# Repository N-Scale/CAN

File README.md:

Ich baue und entwickle Hard- und Software für das Märklin CAN System, weitere Informationen auf  <a href="https://www.stummiforum.de/"> stummiforum.de </a>

Viele Layouts sind Weiterentwicklungen oder Anpassungen an bestehenden Dateien aus dem MaeCAN Projekt.
Hier möchte ich gerne mein Daten mit euch Teilen damit alle die das Märklin CAN System einsetzen wollen davon profitieren können.

Ich versuche die Komponenten an eigener Hardware zu testen, jedoch habe ich nur begrenzt 
Zugriff auf verschiedene Steuereinheiten. Ich kann also nur mit meiner Hardware die Funktionen der Komponenten testen.
Der Nachbau und die Benutzung der Hardware geschieht auf eigene Gefahr, ich hafte nicht für Schäden, die der Anwender oder
Dritte durch die Verwendung verursachen.

Alle Daten sind Sie sind lizensiert unter der <a href="https://creativecommons.org/licenses/by-sa/4.0/de">"Creative Commons Attribution Share-Alike" Lizenz</a> - die eine persönliche und kommerzielle Weiterverwertung erlaubt, solange in angemessener Weise die Urheberschaft erwähnt wird und die abgeleitete Arbeit unter der gleichen Lizenz steht.

<br />This work is licensed under a <a rel="license" href="http://creativecommons.org/licenses/by-sa/4.0/">Creative Commons Attribution-ShareAlike 4.0 International License</a>.

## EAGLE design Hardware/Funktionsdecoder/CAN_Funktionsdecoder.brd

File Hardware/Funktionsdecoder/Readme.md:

Funktionsdecoderaufsatz für das Basisboard.

Ich versuche die Komponenten an eigener Hardware zu testen, jedoch habe ich nur begrenzt 
Zugriff auf verschiedene Steuereinheiten. Ich kann also nur mit meiner Hardware die Funktionen der Komponenten testen.
Der Nachbau und die Benutzung der Hardware geschieht auf eigene Gefahr, ich hafte nicht für Schäden, die der Anwender oder
Dritte durch die Verwendung verursachen.

Alle Daten sind Sie sind lizensiert unter der <a href="https://creativecommons.org/licenses/by-sa/4.0/de">"Creative Commons Attribution Share-Alike" Lizenz</a> - die eine persönliche und kommerzielle Weiterverwertung erlaubt, solange in angemessener Weise die Urheberschaft erwähnt wird und die abgeleitete Arbeit unter der gleichen Lizenz steht.

<br />This work is licensed under a <a rel="license" href="http://creativecommons.org/licenses/by-sa/4.0/">Creative Commons Attribution-ShareAlike 4.0 International License</a>.

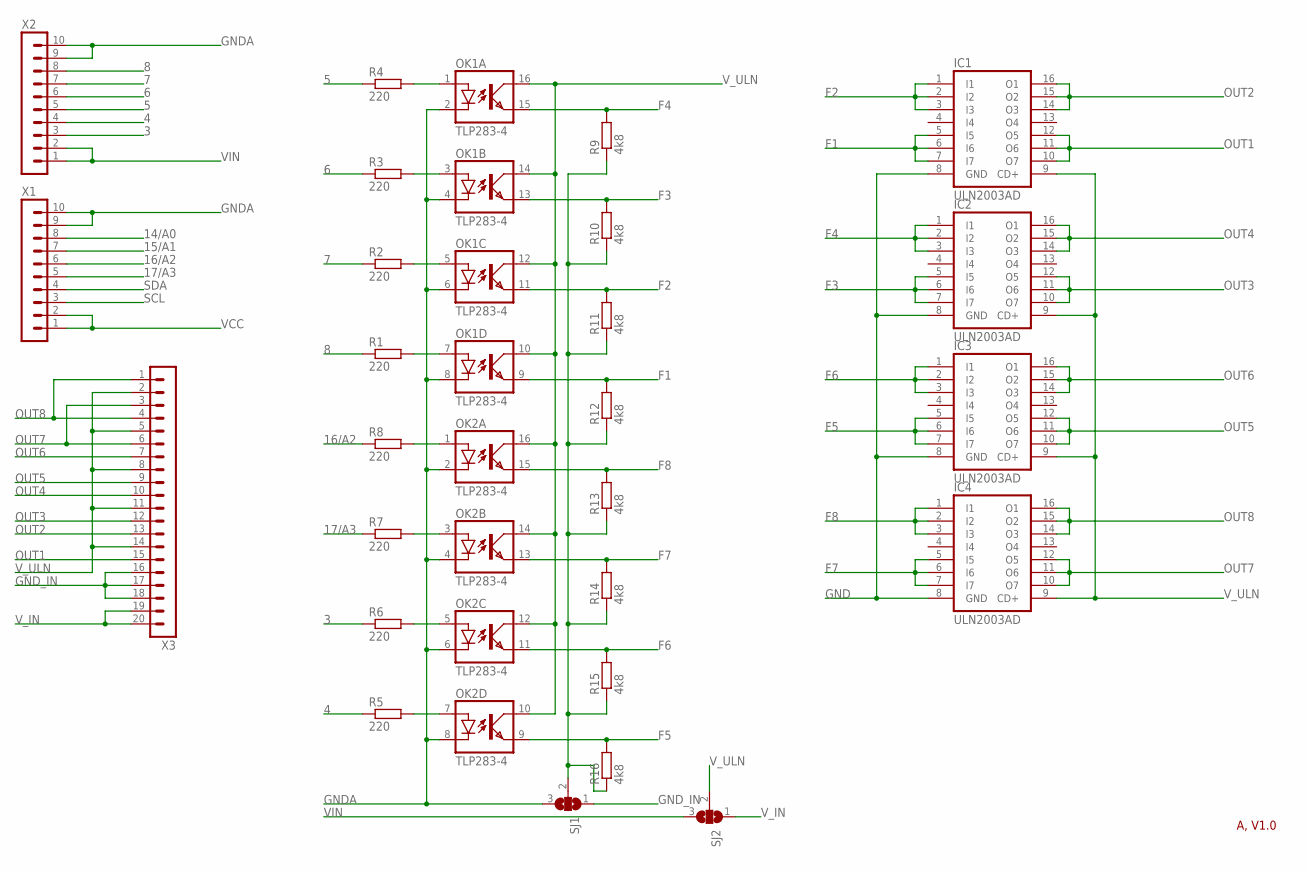
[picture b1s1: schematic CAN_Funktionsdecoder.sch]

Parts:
IC1, IC2, IC3, IC4: ULN2003AD; SO16
OK1, OK2: TLP283-4; MINI-FLAT-16
R1, R2, R3, R4, R5, R6, R7, R8: 220; R0805
R9, R10, R11, R12, R13, R14, R15, R16: 4k8; R0805
SJ1, SJ2: SJ2W; SJ_2
X1, X2: MA10-1
X3: MA20-1

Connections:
3: R6.1, X2.3
4: R5.1, X2.4
5: R4.1, X2.5
6: R3.1, X2.6
7: R2.1, X2.7
8: R1.1, X2.8
14/A0: X1.8
15/A1: X1.7
16/A2: R8.1, X1.6
17/A3: R7.1, X1.5
F1: IC1.5 (I5), IC1.6 (I6), IC1.7 (I7), OK1.9 (EMIT), R12.2
F2: IC1.1 (I1), IC1.2 (I2), IC1.3 (I3), OK1.11 (EMIT), R11.2
F3: IC2.5 (I5), IC2.6 (I6), IC2.7 (I7), OK1.13 (EMIT), R10.2
F4: IC2.1 (I1), IC2.2 (I2), IC2.3 (I3), OK1.15 (EMIT), R9.2
F5: IC3.5 (I5), IC3.6 (I6), IC3.7 (I7), OK2.9 (EMIT), R16.2
F6: IC3.1 (I1), IC3.2 (I2), IC3.3 (I3), OK2.11 (EMIT), R15.2
F7: IC4.5 (I5), IC4.6 (I6), IC4.7 (I7), OK2.13 (EMIT), R14.2
F8: IC4.1 (I1), IC4.2 (I2), IC4.3 (I3), OK2.15 (EMIT), R13.2
GND: IC1.8 (GND), IC2.8 (GND), IC3.8 (GND), IC4.8 (GND), R9.1, R10.1, R11.1, R12.1, R13.1, R14.1, R15.1, R16.1, SJ1.2
GNDA: OK1.2 (C), OK1.4 (C), OK1.6 (C), OK1.8 (C), OK2.2 (C), OK2.4 (C), OK2.6 (C), OK2.8 (C), SJ1.3, X1.9, X1.10, X2.9, X2.10
GND_IN: SJ1.1, X3.16, X3.17, X3.18
unnamed: OK1.3 (A), R3.2
unnamed: OK1.1 (A), R4.2
unnamed: OK1.5 (A), R2.2
unnamed: OK1.7 (A), R1.2
unnamed: OK2.1 (A), R8.2
unnamed: OK2.3 (A), R7.2
unnamed: OK2.5 (A), R6.2
unnamed: OK2.7 (A), R5.2
OUT1: IC1.10 (O7), IC1.11 (O6), IC1.12 (O5), X3.15
OUT2: IC1.14 (O3), IC1.15 (O2), IC1.16 (O1), X3.13
OUT3: IC2.10 (O7), IC2.11 (O6), IC2.12 (O5), X3.12
OUT4: IC2.14 (O3), IC2.15 (O2), IC2.16 (O1), X3.10
OUT5: IC3.10 (O7), IC3.11 (O6), IC3.12 (O5), X3.9
OUT6: IC3.14 (O3), IC3.15 (O2), IC3.16 (O1), X3.7
OUT7: IC4.10 (O7), IC4.11 (O6), IC4.12 (O5), X3.3, X3.6
OUT8: IC4.14 (O3), IC4.15 (O2), IC4.16 (O1), X3.1, X3.4
SCL: X1.3
SDA: X1.4
VCC: X1.1, X1.2
VIN: SJ2.3, X2.1, X2.2
V_IN: SJ2.1, X3.19, X3.20
V_ULN: IC1.9 (CD+), IC2.9 (CD+), IC3.9 (CD+), IC4.9 (CD+), OK1.10 (COL), OK1.12 (COL), OK1.14 (COL), OK1.16 (COL), OK2.10 (COL), OK2.12 (COL), OK2.14 (COL), OK2.16 (COL), SJ2.2, X3.2, X3.5, X3.8, X3.11, X3.14

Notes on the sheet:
A, V1.0

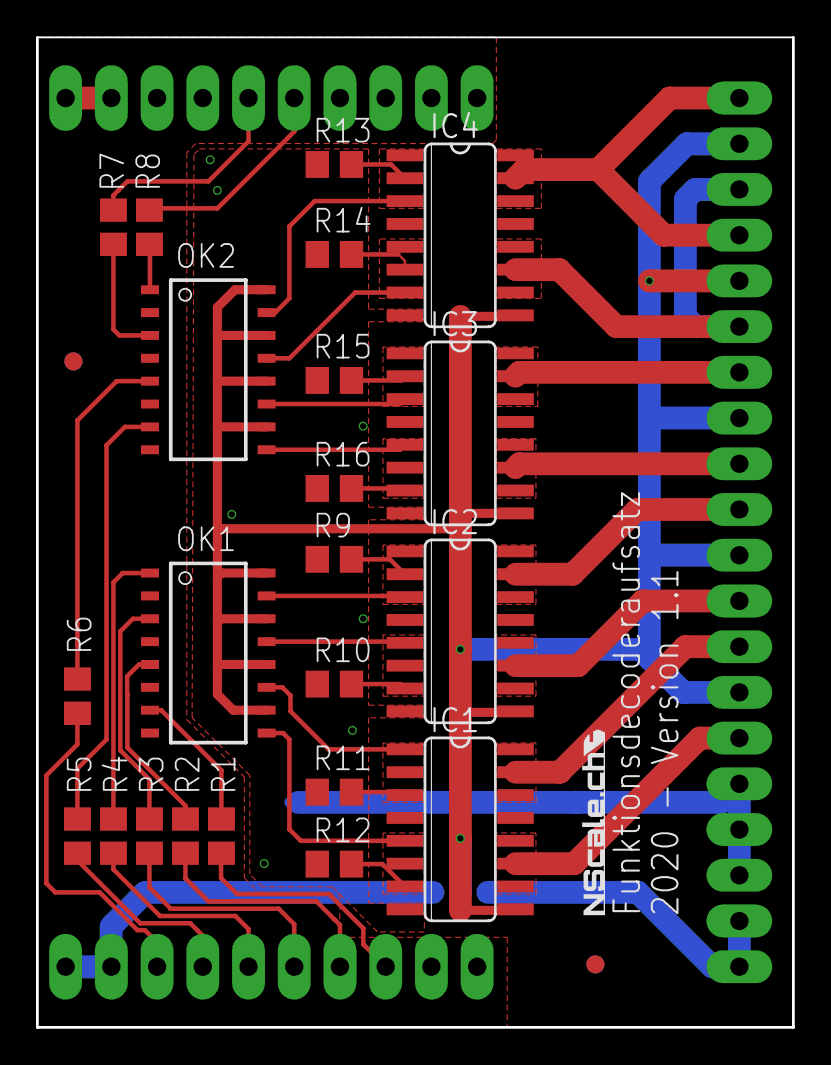
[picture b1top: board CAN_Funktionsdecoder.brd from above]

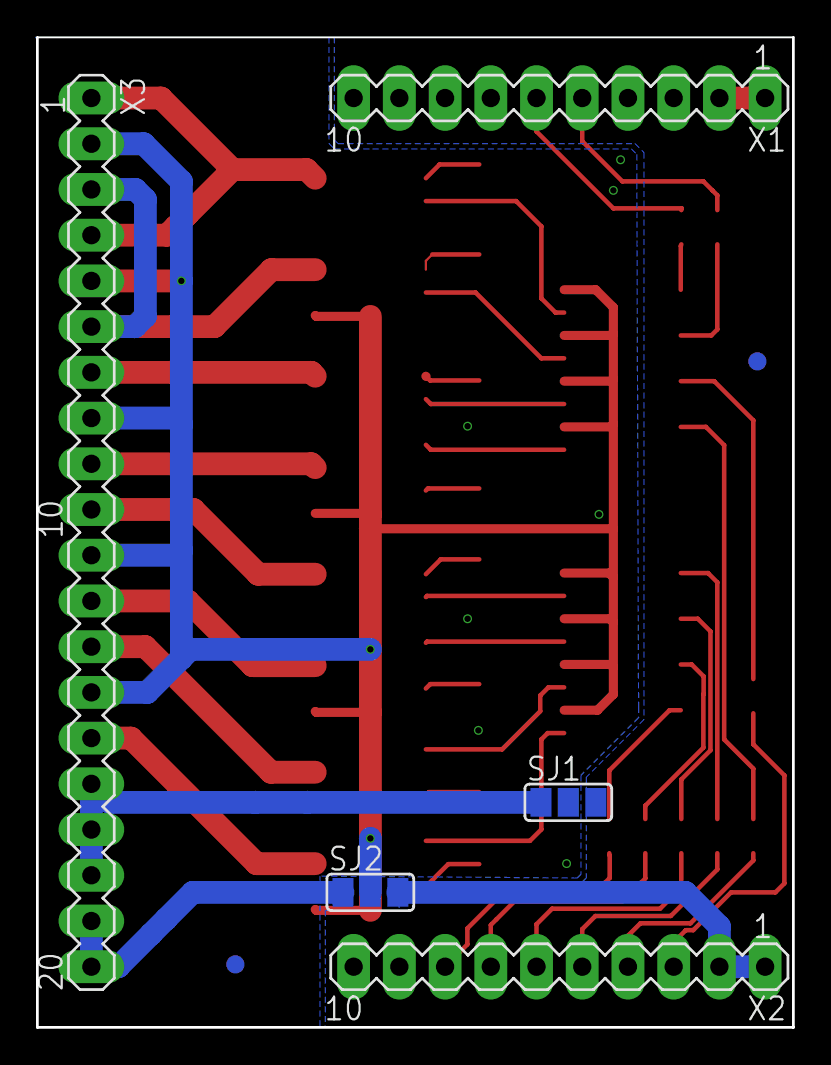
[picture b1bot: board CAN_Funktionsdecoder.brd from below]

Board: 2 copper layers, 42.0 x 55.0 mm, 29 parts (5 on the bottom side), 39 nets.

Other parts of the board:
U$1, U$2: CIRCLE-1MM-3R

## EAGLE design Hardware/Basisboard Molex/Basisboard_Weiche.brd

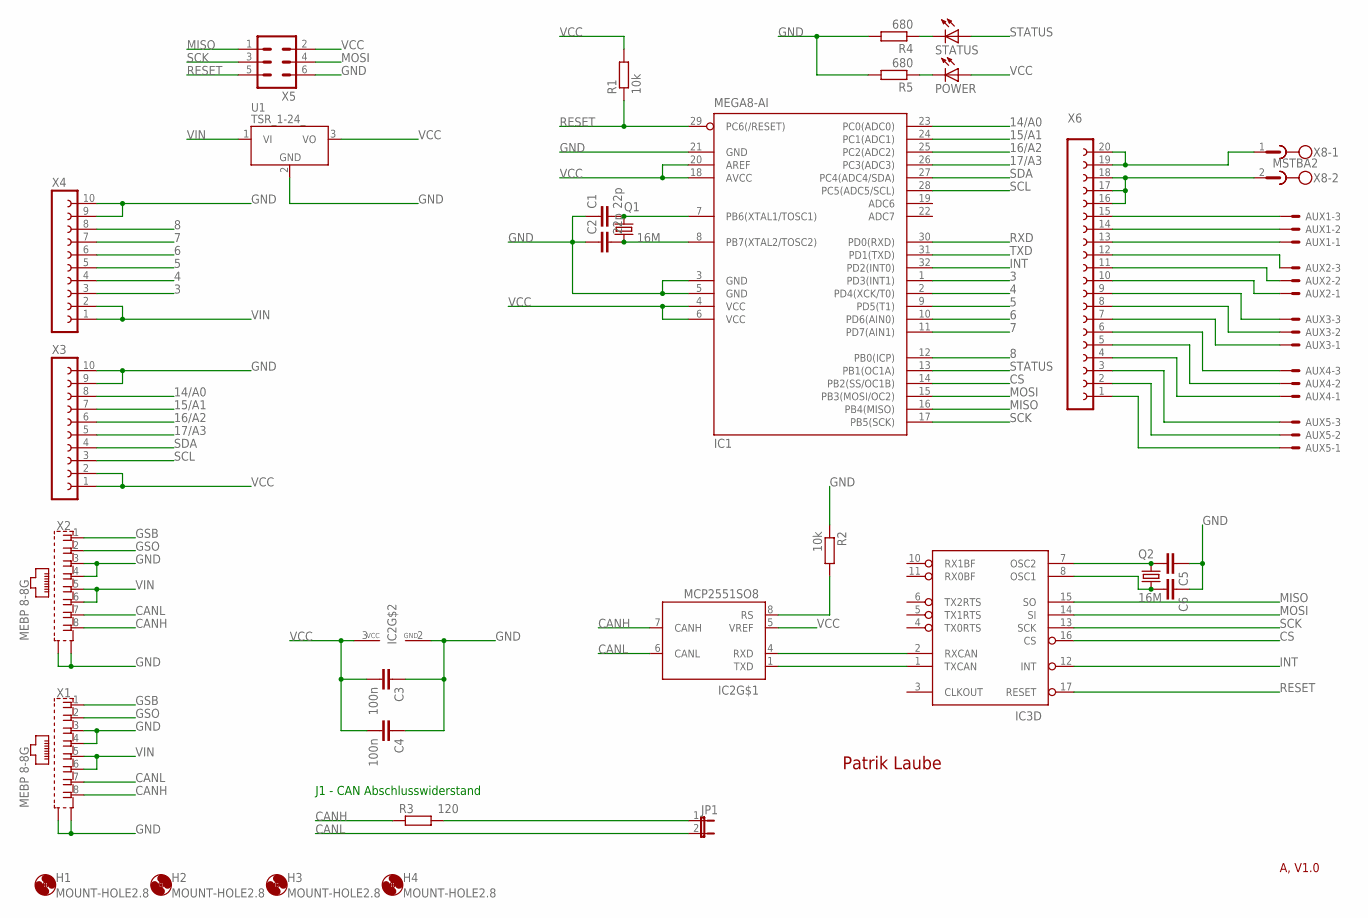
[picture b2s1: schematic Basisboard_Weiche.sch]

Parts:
AUX1, AUX2, AUX3, AUX4, AUX5: 22-27-2031-03; 6410-03
C1, C2: 22p; C1206
C3, C4: 100n; C1206; LCSC_PART C24497
C5, C6: C-EUC1206; C1206
H1, H2, H3, H4: MOUNT-HOLE2.8; 2,8
IC1: MEGA8-AI; TQFP32-08; LCSC_PART C132230
IC2: MCP2551SO8; SO08; LCSC_PART C49558
IC3: MCP2515SO; SO-18W; LCSC_PART C153782
JP1: JP1E; JP1
POWER: LEDCHIPLED_1206; CHIPLED_1206; LCSC_PART C88326
Q1, Q2: 16M; HC49/S
R1, R2: 10k; R1206; LCSC_PART C17902
R3: 120; R1206
R4, R5: 680; R1206
STATUS: LEDCHIPLED_1206; CHIPLED_1206
U1: TSR_1-24_; TSR-1
X1, X2: MEBP 8-8G; XRJF-01A-0-D2A-010
X3, X4: FE10-1; FE10
X5: ML6
X6: FE20-1; FE20
X8: MSTBA2

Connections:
3: IC1.1 (PD3(INT1)), X4.3
4: IC1.2 (PD4(XCK/T0)), X4.4
5: IC1.9 (PD5(T1)), X4.5
6: IC1.10 (PD6(AIN0)), X4.6
7: IC1.11 (PD7(AIN1)), X4.7
8: IC1.12 (PB0(ICP)), X4.8
14/A0: IC1.23 (PC0(ADC0)), X3.8
15/A1: IC1.24 (PC1(ADC1)), X3.7
16/A2: IC1.25 (PC2(ADC2)), X3.6
17/A3: IC1.26 (PC3(ADC3)), X3.5
CANH: IC2.7 (CANH), R3.1, X1.8, X2.8
CANL: IC2.6 (CANL), JP1.2, X1.7, X2.7
CS: IC1.14 (PB2(SS/OC1B)), IC3.16 (CS)
GND: C1.1, C2.1, C3.1, C4.1, C5.1, C6.1, IC1.3 (GND), IC1.5 (GND), IC1.21 (GND), IC2.2 (GND), IC3.9 (GND), R2.1, R4.2, R5.2, U1.2 (GND), X1.3, X1.4, X1.S1 (S), X1.S2 (S), X2.3, X2.4, X2.S1 (S), X2.S2 (S), X3.9, X3.10, X4.9, X4.10, X5.6
GSB: X1.1, X2.1
GSO: X1.2, X2.2
INT: IC1.32 (PD2(INT0)), IC3.12 (INT)
MISO: IC1.16 (PB4(MISO)), IC3.15 (SO), X5.1
MOSI: IC1.15 (PB3(MOSI/OC2)), IC3.14 (SI), X5.4
unnamed: IC2.8 (RS), R2.2
unnamed: JP1.1, R3.2
unnamed: IC2.4 (RXD), IC3.2 (RXCAN)
unnamed: AUX1.1, X6.13
unnamed: AUX1.2, X6.14
unnamed: AUX1.3, X6.15
unnamed: C1.2, IC1.7 (PB6(XTAL1/TOSC1)), Q1.2
unnamed: C2.2, IC1.8 (PB7(XTAL2/TOSC2)), Q1.1
unnamed: AUX2.3, X6.12
unnamed: AUX2.2, X6.11
unnamed: AUX2.1, X6.10
unnamed: R4.1, STATUS.C
unnamed: AUX3.3, X6.9
unnamed: AUX3.2, X6.8
unnamed: AUX3.1, X6.7
unnamed: AUX4.3, X6.6
unnamed: AUX4.2, X6.5
unnamed: AUX4.1, X6.4
unnamed: AUX5.3, X6.3
unnamed: AUX5.2, X6.2
unnamed: AUX5.1, X6.1
unnamed: IC2.1 (TXD), IC3.1 (TXCAN)
unnamed: X6.16, X6.17, X6.18, X8.2
unnamed: X6.19, X6.20, X8.1
unnamed: POWER.C, R5.1
unnamed: C6.2, IC3.8 (OSC1), Q2.2
unnamed: C5.2, IC3.7 (OSC2), Q2.1
RESET: IC1.29 (PC6(/RESET)), IC3.17 (RESET), R1.1, X5.5
RXD: IC1.30 (PD0(RXD))
SCK: IC1.17 (PB5(SCK)), IC3.13 (SCK), X5.3
SCL: IC1.28 (PC5(ADC5/SCL)), X3.3
SDA: IC1.27 (PC4(ADC4/SDA)), X3.4
STATUS: IC1.13 (PB1(OC1A)), STATUS.A
TXD: IC1.31 (PD1(TXD))
VCC: C3.2, C4.2, IC1.4 (VCC), IC1.6 (VCC), IC1.18 (AVCC), IC1.20 (AREF), IC2.3 (VCC), IC2.5 (VREF), IC3.18 (VCC), POWER.A, R1.2, U1.3 (VO), X3.1, X3.2, X5.2
VIN: U1.1 (VI), X1.5, X1.6, X2.5, X2.6, X4.1, X4.2

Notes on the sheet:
Patrik Laube
A, V1.0
J1 - CAN Abschlusswiderstand

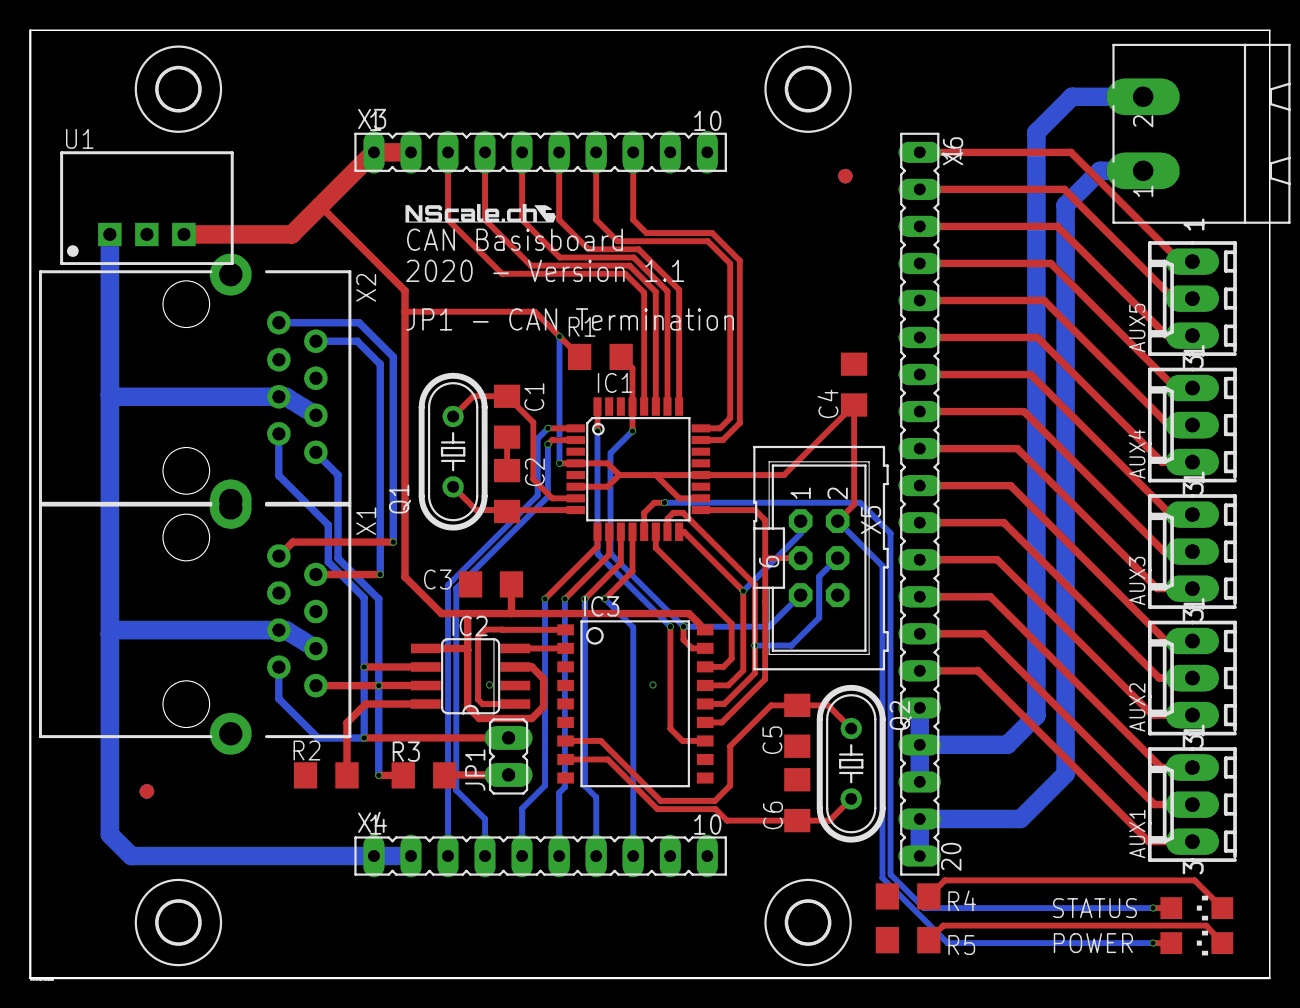
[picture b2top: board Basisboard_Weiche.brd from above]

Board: 2 copper layers, 85.0 x 65.0 mm, 38 parts (0 on the bottom side), 53 nets.

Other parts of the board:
U$1, U$2: CIRCLE-1MM-3R

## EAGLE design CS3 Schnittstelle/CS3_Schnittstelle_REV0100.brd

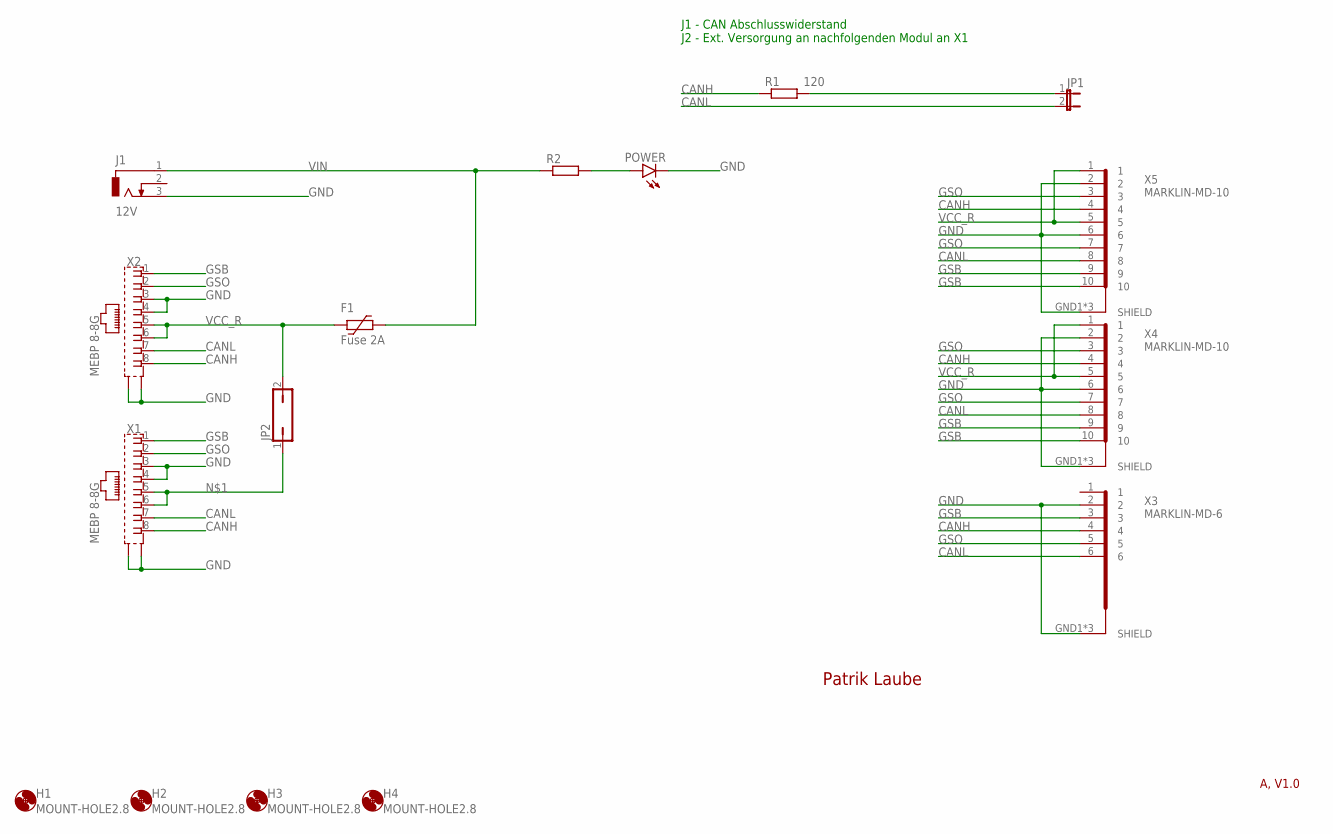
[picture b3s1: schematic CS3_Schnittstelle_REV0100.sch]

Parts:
F1: Fuse 2A; 2920L
H1, H2, H3, H4: MOUNT-HOLE2.8; 2,8
J1: 12V; DCJ0202
JP1: JP1E; JP1
JP2: JP1Q; JP1
POWER: LEDCHIPLED_1206; CHIPLED_1206
R1: 120; R1206
R2: R-EU_R1206; R1206
X1, X2: MEBP 8-8G; XRJF-01A-0-D2A-010
X3: MARKLIN-MD-6; MARKLIN-MD-6-PRINT
X4, X5: MARKLIN-MD-10; MARKLIN-MD-10-PRINT

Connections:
CANH: R1.1, X1.8, X2.8, X3.4, X4.4, X5.4
CANL: JP1.2, X1.7, X2.7, X3.6, X4.8, X5.8
GND: J1.3, POWER.C, X1.3, X1.4, X1.S1 (S), X1.S2 (S), X2.3, X2.4, X2.S1 (S), X2.S2 (S), X3.2, X3.GND1 (SHIELD), X3.GND2 (SHIELD), X3.GND3 (SHIELD), X4.2, X4.6, X4.GND1 (SHIELD), X4.GND2 (SHIELD), X4.GND3 (SHIELD), X5.2, X5.6, X5.GND1 (SHIELD), X5.GND2 (SHIELD), X5.GND3 (SHIELD)
GSB: X1.1, X2.1, X3.3, X4.9, X4.10, X5.9, X5.10
GSO: X1.2, X2.2, X3.5, X4.3, X4.7, X5.3, X5.7
unnamed: JP2.1, X1.5, X1.6
unnamed: JP1.1, R1.2
unnamed: POWER.A, R2.2
VCC_R: F1.2, JP2.2, X2.5, X2.6, X4.1, X4.5, X5.1, X5.5
VIN: F1.1, J1.1, R2.1

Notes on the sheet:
Patrik Laube
A, V1.0
J1 - CAN Abschlusswiderstand J2 - Ext. Versorgung an nachfolgenden Modul an X1

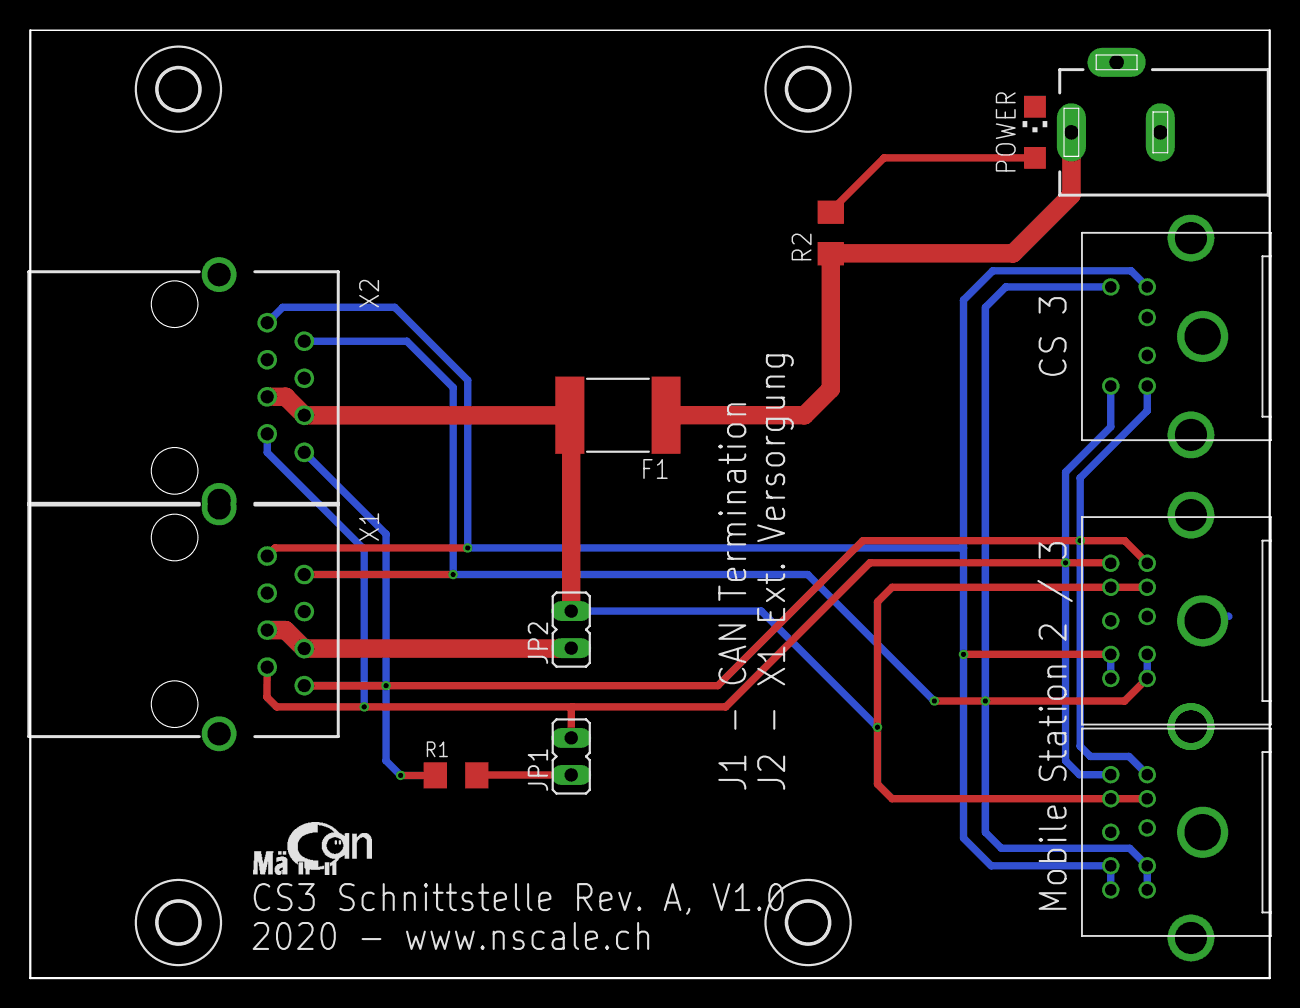
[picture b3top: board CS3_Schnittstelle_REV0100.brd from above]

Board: 2 copper layers, 85.0 x 65.0 mm, 16 parts (0 on the bottom side), 10 nets.

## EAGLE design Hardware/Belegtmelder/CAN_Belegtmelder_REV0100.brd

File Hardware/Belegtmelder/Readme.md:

Belegtmelderaufsatz für das Basisboard.

Ich versuche die Komponenten an eigener Hardware zu testen, jedoch habe ich nur begrenzt 
Zugriff auf verschiedene Steuereinheiten. Ich kann also nur mit meiner Hardware die Funktionen der Komponenten testen.
Der Nachbau und die Benutzung der Hardware geschieht auf eigene Gefahr, ich hafte nicht für Schäden, die der Anwender oder
Dritte durch die Verwendung verursachen.

Alle Daten sind Sie sind lizensiert unter der <a href="https://creativecommons.org/licenses/by-sa/4.0/de">"Creative Commons Attribution Share-Alike" Lizenz</a> - die eine persönliche und kommerzielle Weiterverwertung erlaubt, solange in angemessener Weise die Urheberschaft erwähnt wird und die abgeleitete Arbeit unter der gleichen Lizenz steht.

<br />This work is licensed under a <a rel="license" href="http://creativecommons.org/licenses/by-sa/4.0/">Creative Commons Attribution-ShareAlike 4.0 International License</a>.

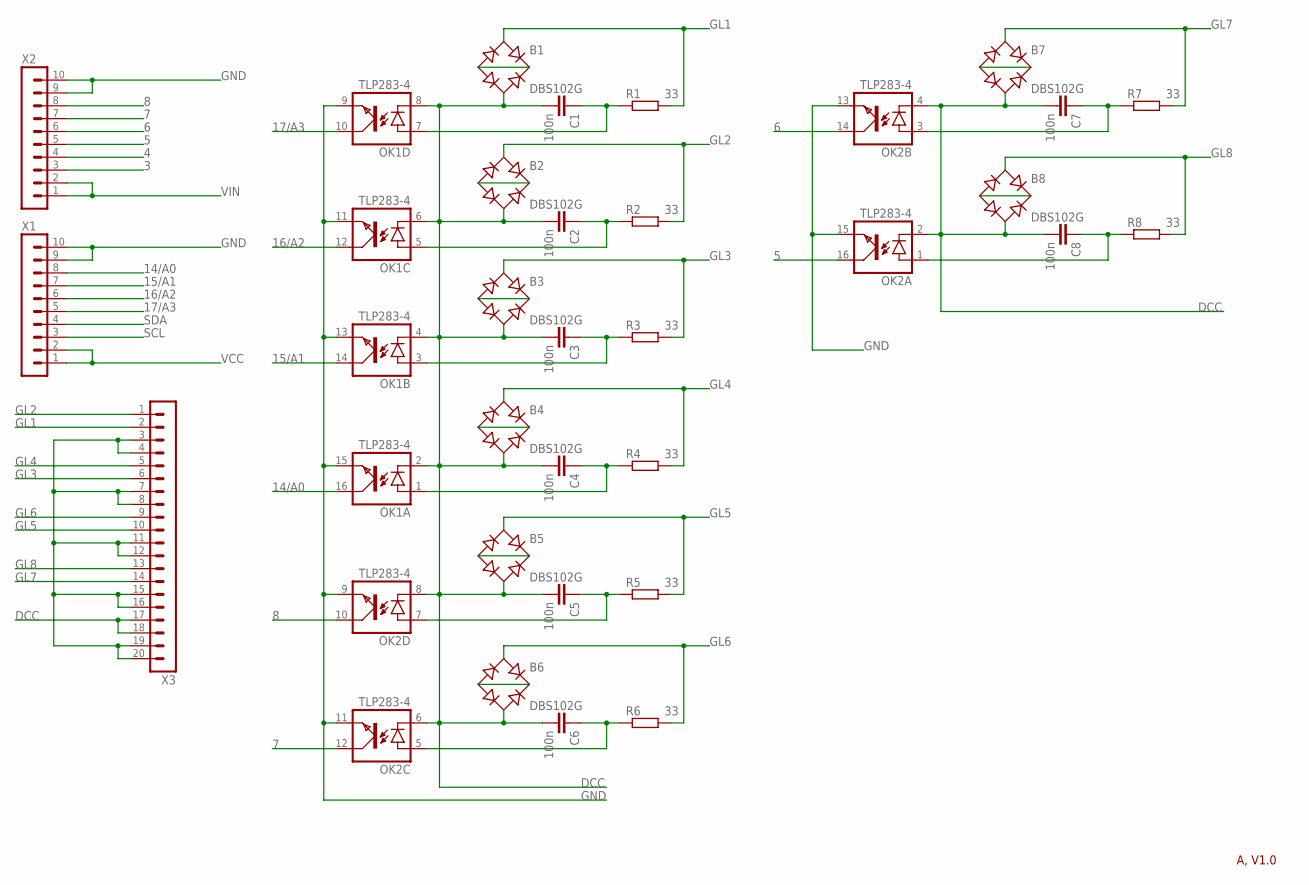
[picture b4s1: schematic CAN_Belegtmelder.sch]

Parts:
B1, B2, B3, B4, B5, B6, B7, B8: DBS102G; DBS
C1, C2, C3, C4, C5, C6, C7, C8: 100n; C1206
OK1, OK2: TLP283-4; MINI-FLAT-16
R1, R2, R3, R4, R5, R6, R7, R8: 33; R1206
X1, X2: MA10-1
X3: MA20-1

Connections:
3: X2.3
4: X2.4
5: OK2.16 (COL), X2.5
6: OK2.14 (COL), X2.6
7: OK2.12 (COL), X2.7
8: OK2.10 (COL), X2.8
14/A0: OK1.16 (COL), X1.8
15/A1: OK1.14 (COL), X1.7
16/A2: OK1.12 (COL), X1.6
17/A3: OK1.10 (COL), X1.5
DCC: B1.AC2, B2.AC2, B3.AC2, B4.AC2, B5.AC2, B6.AC2, B7.AC2, B8.AC2, C1.2, C2.2, C3.2, C4.2, C5.2, C6.2, C7.2, C8.2, OK1.2 (C), OK1.4 (C), OK1.6 (C), OK1.8 (C), OK2.2 (C), OK2.4 (C), OK2.6 (C), OK2.8 (C), X3.17, X3.18
GL1: B1.AC1, R1.2, X3.2
GL2: B2.AC1, R2.2, X3.1
GL3: B3.AC1, R3.2, X3.6
GL4: B4.AC1, R4.2, X3.5
GL5: B5.AC1, R5.2, X3.10
GL6: B6.AC1, R6.2, X3.9
GL7: B7.AC1, R7.2, X3.14
GL8: B8.AC1, R8.2, X3.13
GND: OK1.9 (EMIT), OK1.11 (EMIT), OK1.13 (EMIT), OK1.15 (EMIT), OK2.9 (EMIT), OK2.11 (EMIT), OK2.13 (EMIT), OK2.15 (EMIT), X1.9, X1.10, X2.9, X2.10
unnamed: C1.1, OK1.7 (A), R1.1
unnamed: B1.+, B1.-
unnamed: B2.+, B2.-
unnamed: C2.1, OK1.5 (A), R2.1
unnamed: B3.+, B3.-
unnamed: C3.1, OK1.3 (A), R3.1
unnamed: B4.+, B4.-
unnamed: C4.1, OK1.1 (A), R4.1
unnamed: B5.+, B5.-
unnamed: C5.1, OK2.7 (A), R5.1
unnamed: B6.+, B6.-
unnamed: C6.1, OK2.5 (A), R6.1
unnamed: B7.+, B7.-
unnamed: C7.1, OK2.3 (A), R7.1
unnamed: B8.+, B8.-
unnamed: C8.1, OK2.1 (A), R8.1
unnamed: X3.3, X3.4, X3.7, X3.8, X3.11, X3.12, X3.15, X3.16, X3.19, X3.20
SCL: X1.3
SDA: X1.4
VCC: X1.1, X1.2
VIN: X2.1, X2.2

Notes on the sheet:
A, V1.0

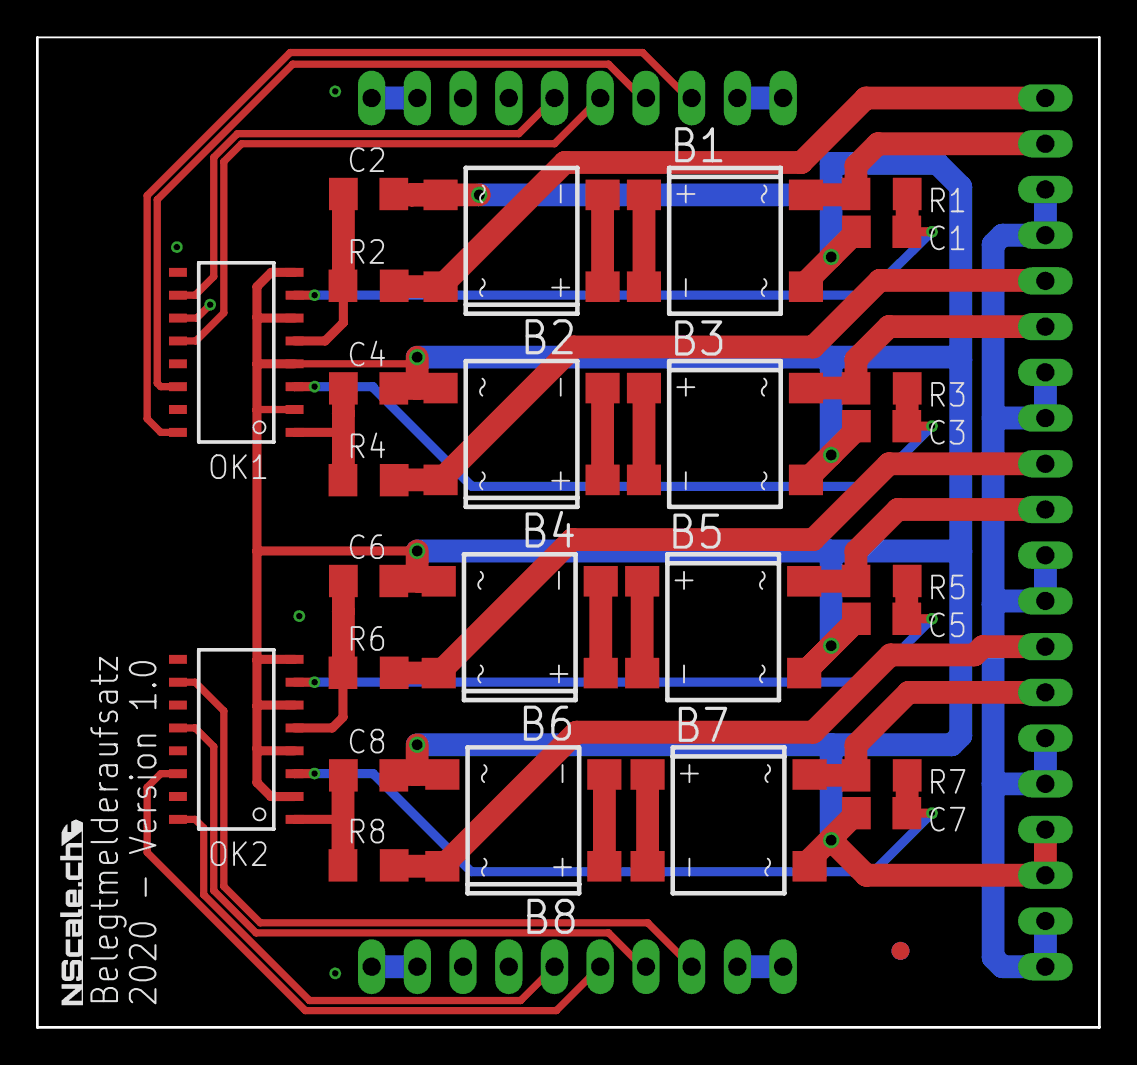
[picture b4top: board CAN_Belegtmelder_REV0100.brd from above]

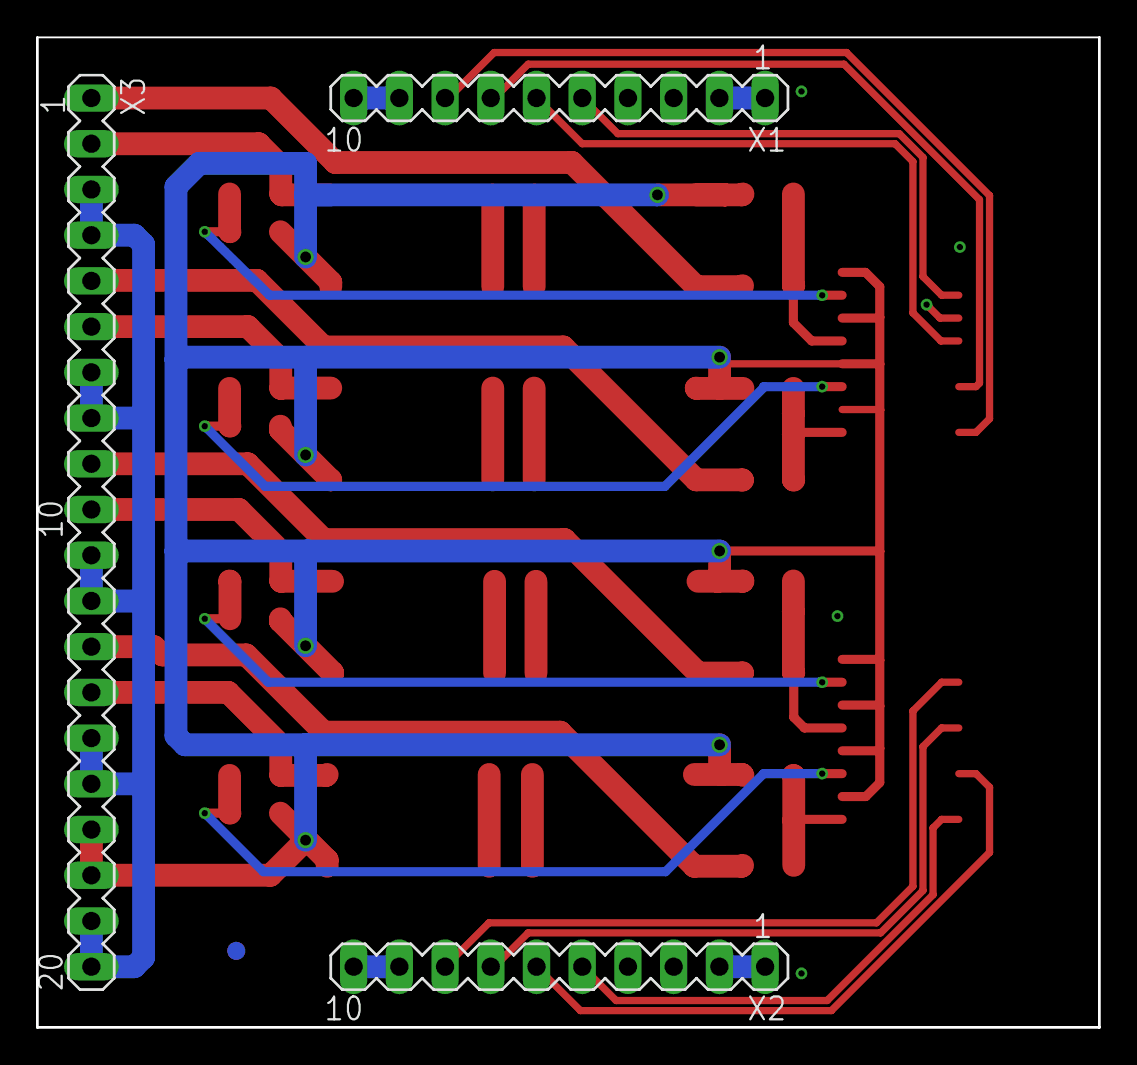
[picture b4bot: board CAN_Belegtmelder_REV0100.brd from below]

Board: 2 copper layers, 59.0 x 55.0 mm, 30 parts (3 on the bottom side), 37 nets.

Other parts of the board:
U$2: CIRCLE-1MM-3R

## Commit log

2020-01-02 Rename CS3 Schnittstelle/CS3_Schnittstelle_REV0100.brd to Hardware/CS3 Schnittstelle/CS3_Schnittstelle_REV0100.brd
2020-01-02 Rename CS3 Schnittstelle/CS3_Schnittstelle_REV0100.sch to Hardware/CS3 Schnittstelle/CS3_Schnittstelle_REV0100.sch
2020-01-02 Rename CS3 Schnittstelle/Readme to Hardware/CS3 Schnittstelle/Readme
2020-02-09 Rename Readme to Readme.md
2021-03-09 REV0101
2021-03-09 Upload Funktionsdecoder
2021-03-09 Upload Belegtmelder
2021-03-09 Upload CS3 Schnittstelle
